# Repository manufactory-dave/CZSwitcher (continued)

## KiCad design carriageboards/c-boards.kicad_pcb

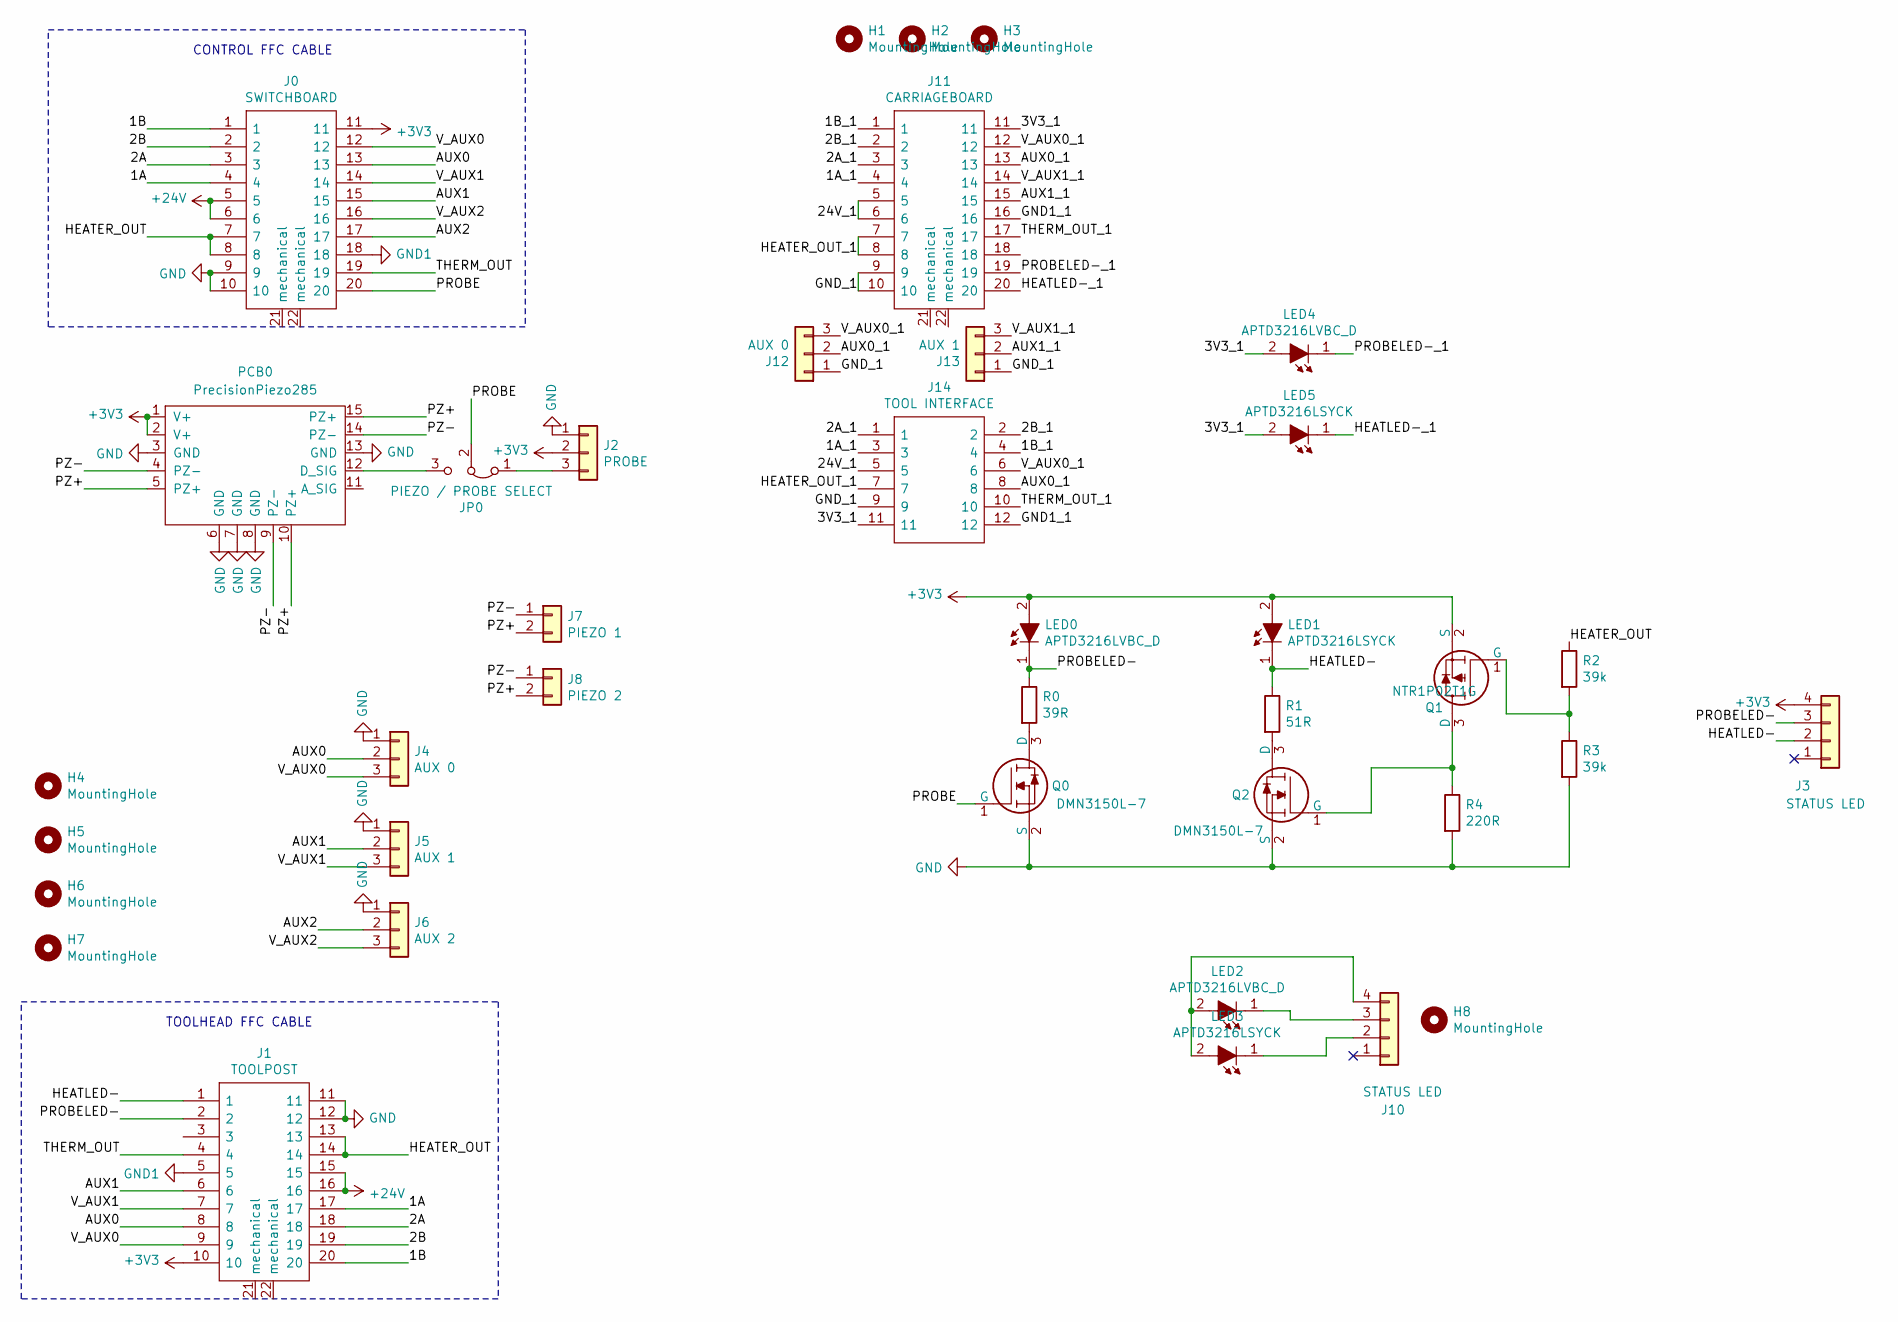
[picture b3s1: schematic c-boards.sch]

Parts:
H1, H2, H3, H4, H5, H6, H7, H8: MountingHole; MountingHole_2.7mm_M2.5
J0: SWITCHBOARD; ZF1-20-XX-ZZ-WT_Handsolder; Manufacturer_Part_Number ZF1-20-01-T-WT
J1: TOOLPOST; ZF1-20-XX-ZZ-WT_Handsolder; Manufacturer_Part_Number ZF1-20-01-T-WT
J2: PROBE; JST_XH_S3B-XH-A_1x03_P2.50mm_Horizontal
J3, J10: STATUS LED; JST-ZH_S4B-ZR-SM4A-TF
J4: AUX 0; JST_XH_S3B-XH-A_1x03_P2.50mm_Horizontal
J5: AUX 1; JST_XH_S3B-XH-A_1x03_P2.50mm_Horizontal
J6: AUX 2; JST_XH_S3B-XH-A_1x03_P2.50mm_Horizontal
J7: PIEZO 1; JST-ZH_S2B-ZR-SM4A-TF; Part No S2B-ZR-SM4A-TF
J8: PIEZO 2; JST-ZH_S2B-ZR-SM4A-TF; Part No S2B-ZR-SM4A-TF
J11: CARRIAGEBOARD; ZF1-20-XX-ZZ-WT_Handsolder; Manufacturer_Part_Number ZF1-20-01-T-WT
J12: AUX 0; JST-XH_2.50MM_03x01_SMT
J13: AUX 1; JST-XH_2.50MM_03x01_SMT
J14: TOOL INTERFACE; 813-S1-012-10-014101; Manufacturer_Part_Number 813-S1-012-10-014101
JP0: PIEZO / PROBE SELECT; PinHeader_1x03_P2.54mm_Vertical
LED0, LED2, LED4: APTD3216LVBC_D; LED_1206_3216Metric_Pad1.42x1.75mm_HandSolder; Manufacturer_Part_Number APTD3216LVBC/D
LED1, LED3, LED5: APTD3216LSYCK; LED_1206_3216Metric_Pad1.42x1.75mm_HandSolder; Manufacturer_Part_Number APTD3216LSYCK
PCB0: PrecisionPiezo285; Precision_Piezo_2.85
Q0, Q2: DMN3150L-7; SUPER-SOT-3; Manufacturer_Part_Number DMN3150L-7
Q1: NTR1P02T1G; SUPER-SOT-3; Manufacturer_Part_Number NTR1P02T1G
R0: 39R; R_0805_2012Metric_Pad1.20x1.40mm_HandSolder; Manufacturer_Part_Number RK73B2ATTD390J
R1: 51R; R_0805_2012Metric_Pad1.20x1.40mm_HandSolder; Manufacturer_Part_Number RK73B2ATTD510J
R2: 39k; R_0805_2012Metric_Pad1.20x1.40mm_HandSolder; Manufacturer_Part_Number RK73B2ATTD393J
R3: 39k; R_0805_2012Metric_Pad1.20x1.40mm_HandSolder; Manufacturer_Part_Number RK73B2ATTD103J
R4: 220R; R_0805_2012Metric_Pad1.20x1.40mm_HandSolder; Manufacturer_Part_Number RK73B2ATTD510J

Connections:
+3V3: J0.11, J1.10, J2.2, J3.4, LED0.2, LED1.2, PCB0.1 (V+), PCB0.2 (V+), Q1.2 (S)
+24V: J0.5, J0.6, J1.15, J1.16
/1A: J0.4, J1.17
/1A_1: J11.4, J14.3
/1B: J0.1, J1.20
/1B_1: J11.1, J14.4
/2A: J0.3, J1.18
/2A_1: J11.3, J14.1
/2B: J0.2, J1.19
/2B_1: J11.2, J14.2
/3V3_1: J11.11, J14.11, LED4.2, LED5.2
/24V_1: J11.5, J11.6, J14.5
/AUX0: J0.13, J1.8, J4.2
/AUX0_1: J11.13, J12.2, J14.8
/AUX1: J0.15, J1.6, J5.2
/AUX1_1: J11.15, J13.2
/AUX2: J0.17, J6.2
/GND1_1: J11.16, J14.12
/GND_1: J11.9, J11.10, J12.1, J13.1, J14.9
/HEATER_OUT: J0.7, J0.8, J1.13, J1.14, R2.1
/HEATER_OUT_1: J11.7, J11.8, J14.7
/HEATLED-: J1.1, J3.2, LED1.1, R1.1
/HEATLED-_1: J11.20, LED5.1
/PROBE: J0.20, JP0.2 (C), Q0.1 (G)
/PROBELED-: J1.2, J3.3, LED0.1, R0.1
/PROBELED-_1: J11.19, LED4.1
/PZ+: J7.2, J8.2, PCB0.5 (PZ+), PCB0.10 (PZ+), PCB0.15 (PZ+)
/PZ-: J7.1, J8.1, PCB0.4 (PZ-), PCB0.9 (PZ-), PCB0.14 (PZ-)
/THERM_OUT: J0.19, J1.4
/THERM_OUT_1: J11.17, J14.10
/V_AUX0: J0.12, J1.9, J4.3
/V_AUX0_1: J11.12, J12.3, J14.6
/V_AUX1: J0.14, J1.7, J5.3
/V_AUX1_1: J11.14, J13.3
/V_AUX2: J0.16, J6.3
GND: J0.9, J0.10, J1.11, J1.12, J2.1, J4.1, J5.1, J6.1, PCB0.3 (GND), PCB0.6 (GND), PCB0.7 (GND), PCB0.8 (GND), PCB0.13 (GND), Q0.2 (S), Q2.2 (S), R3.2, R4.2
GND1: J0.18, J1.5
unnamed: J2.3, JP0.1 (A)
unnamed: J10.2, LED3.1
unnamed: J10.3, LED2.1
unnamed: J10.4, LED2.2, LED3.2
unnamed: JP0.3 (B), PCB0.12 (D_SIG)
unnamed: Q0.3 (D), R0.2
unnamed: Q1.1 (G), R2.2, R3.1
unnamed: Q1.3 (D), Q2.1 (G), R4.1
unnamed: Q2.3 (D), R1.2

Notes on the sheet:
CONTROL FFC CABLE
TOOLHEAD FFC CABLE

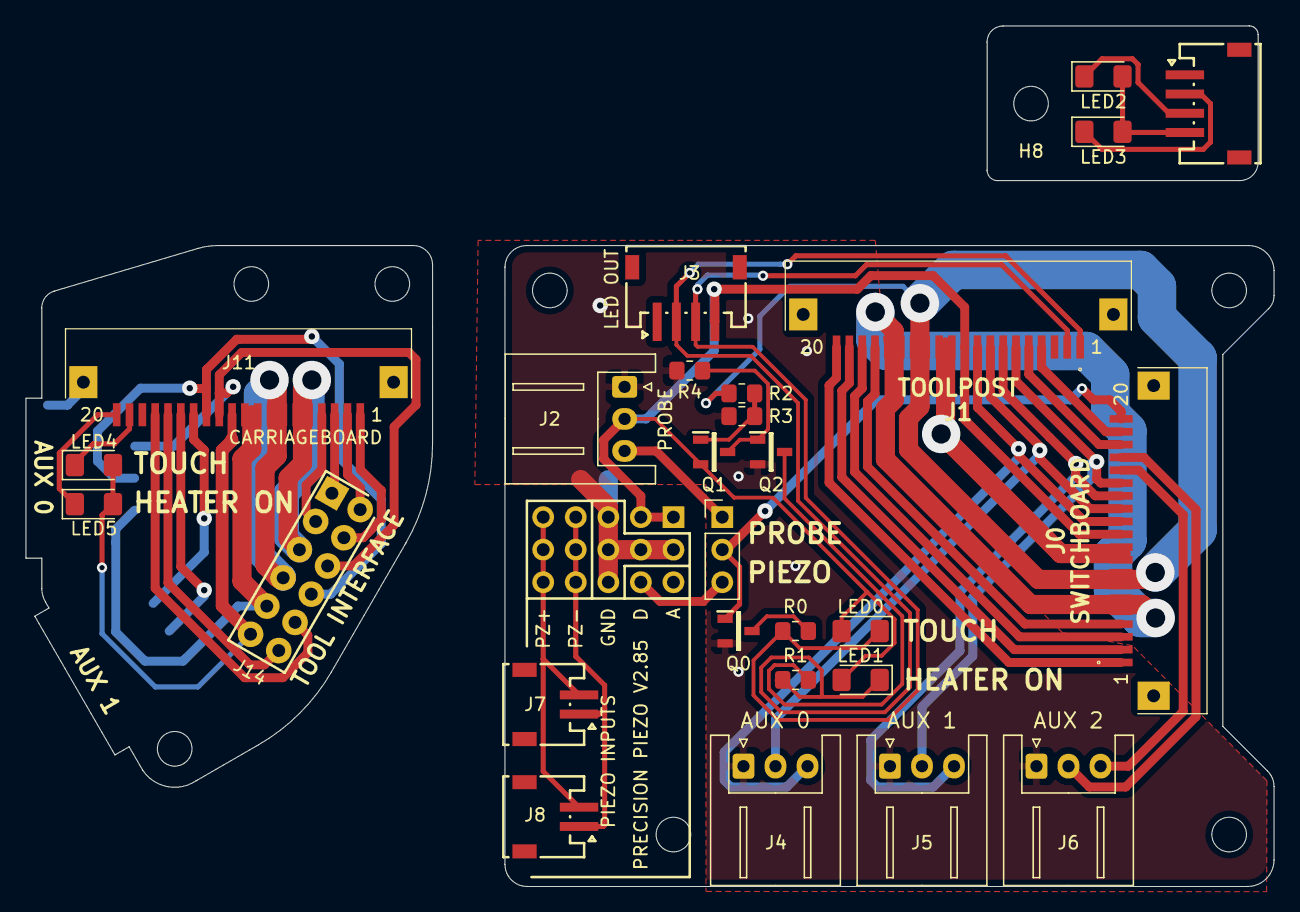
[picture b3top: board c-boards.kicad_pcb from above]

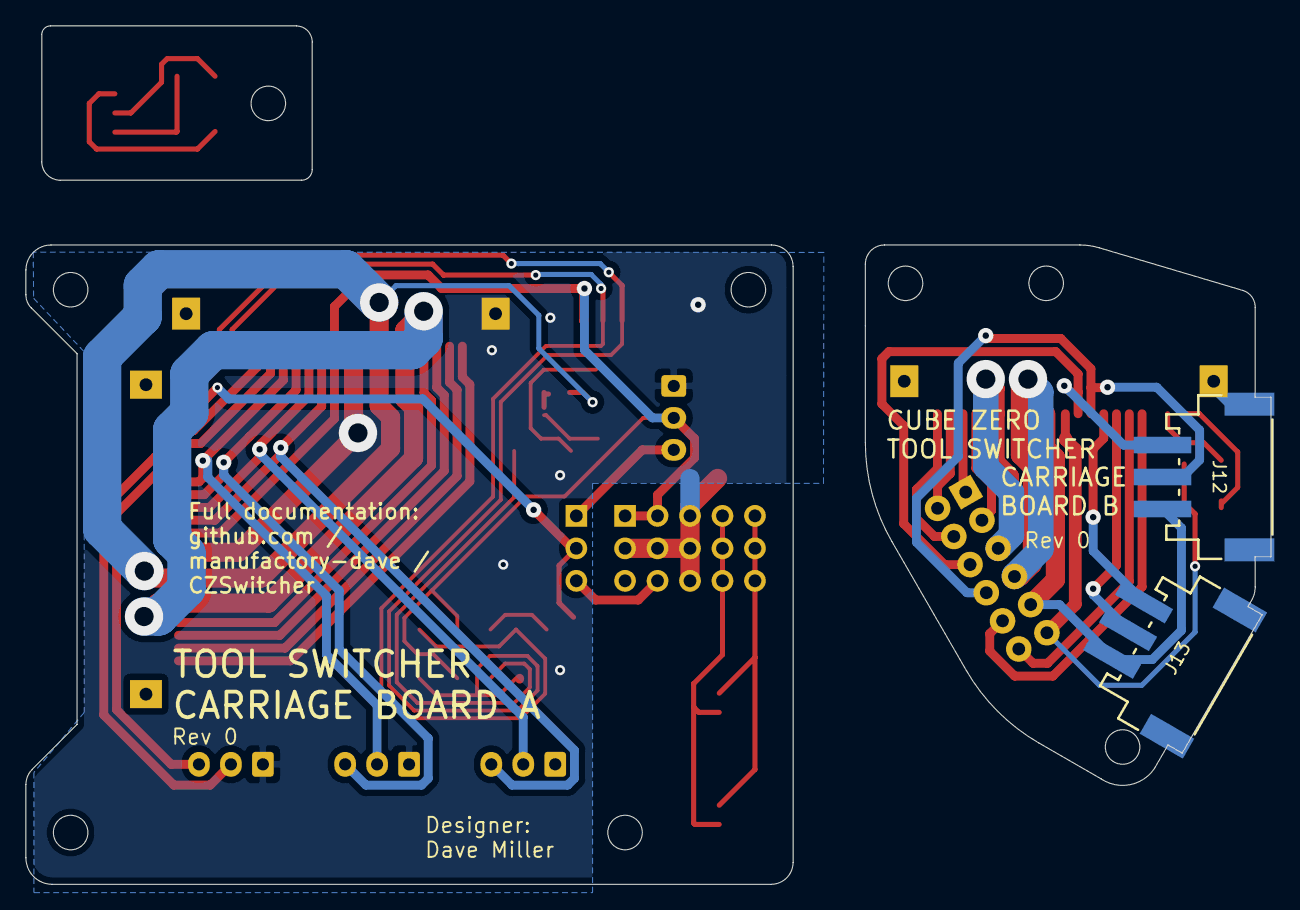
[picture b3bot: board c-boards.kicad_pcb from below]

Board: 2 copper layers, 97.4 x 67.1 mm, 38 parts (2 on the bottom side), 46 nets.

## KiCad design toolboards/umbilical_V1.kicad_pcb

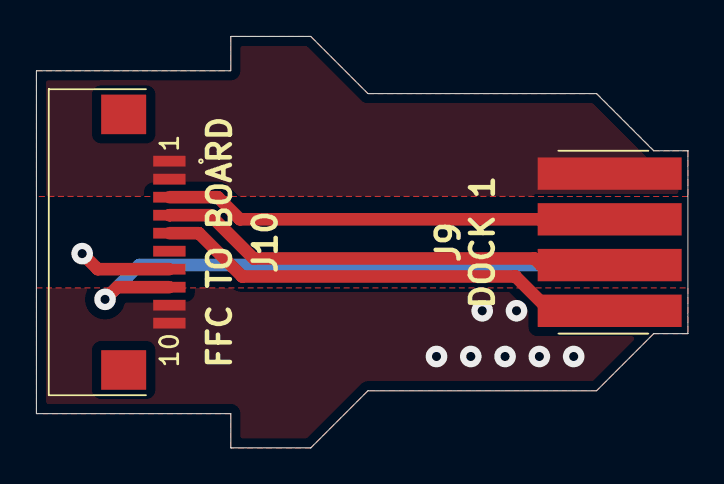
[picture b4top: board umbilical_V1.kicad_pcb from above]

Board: 2 copper layers, 36.2 x 22.9 mm, 3 parts (1 on the bottom side), 7 nets.

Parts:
J9: DOCK 1; 8MM11000402131_handsolder
J10: FFC TO BOARD; ZF1-10-XX-ZZ-WT-TR
J11: DOCK 2; 8MM11000402131_handsolder

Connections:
/3V3_2: J9.3, J10.4
/24V_2: J9.1, J10.1, J10.2
/AUX0_2: J9.4, J10.5
/GND1_2: J9.2, J10.3
/GND_2: J10.7, J11.3
/HEATER_OUT_2: J10.9, J10.10, J11.1
/THERM_OUT_2: J10.8, J11.2
